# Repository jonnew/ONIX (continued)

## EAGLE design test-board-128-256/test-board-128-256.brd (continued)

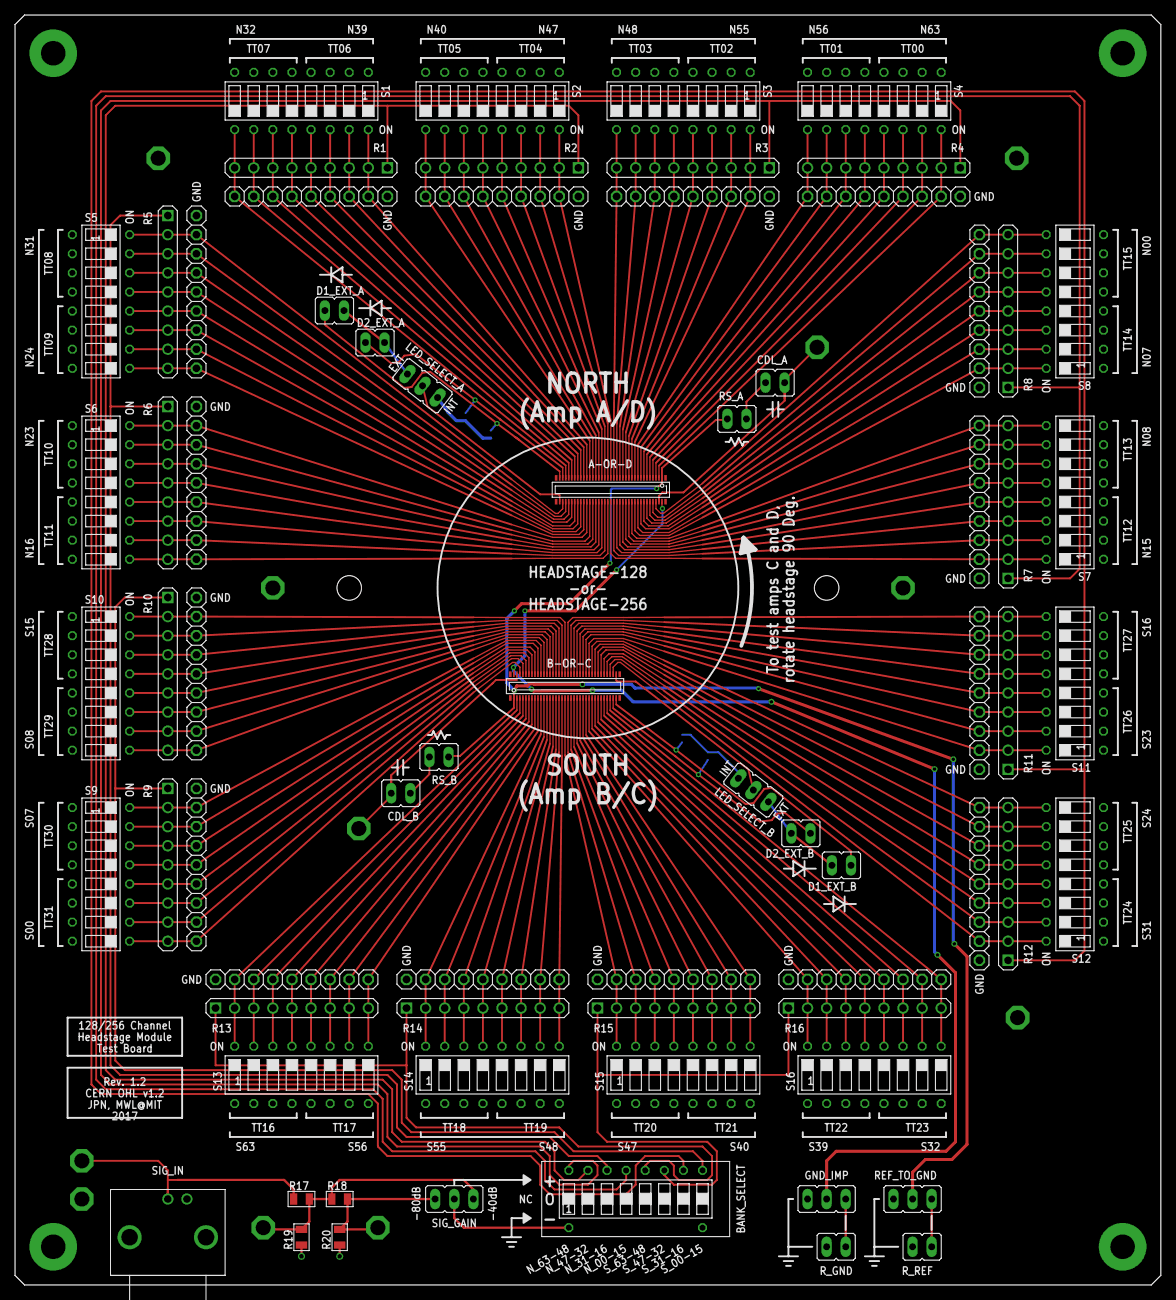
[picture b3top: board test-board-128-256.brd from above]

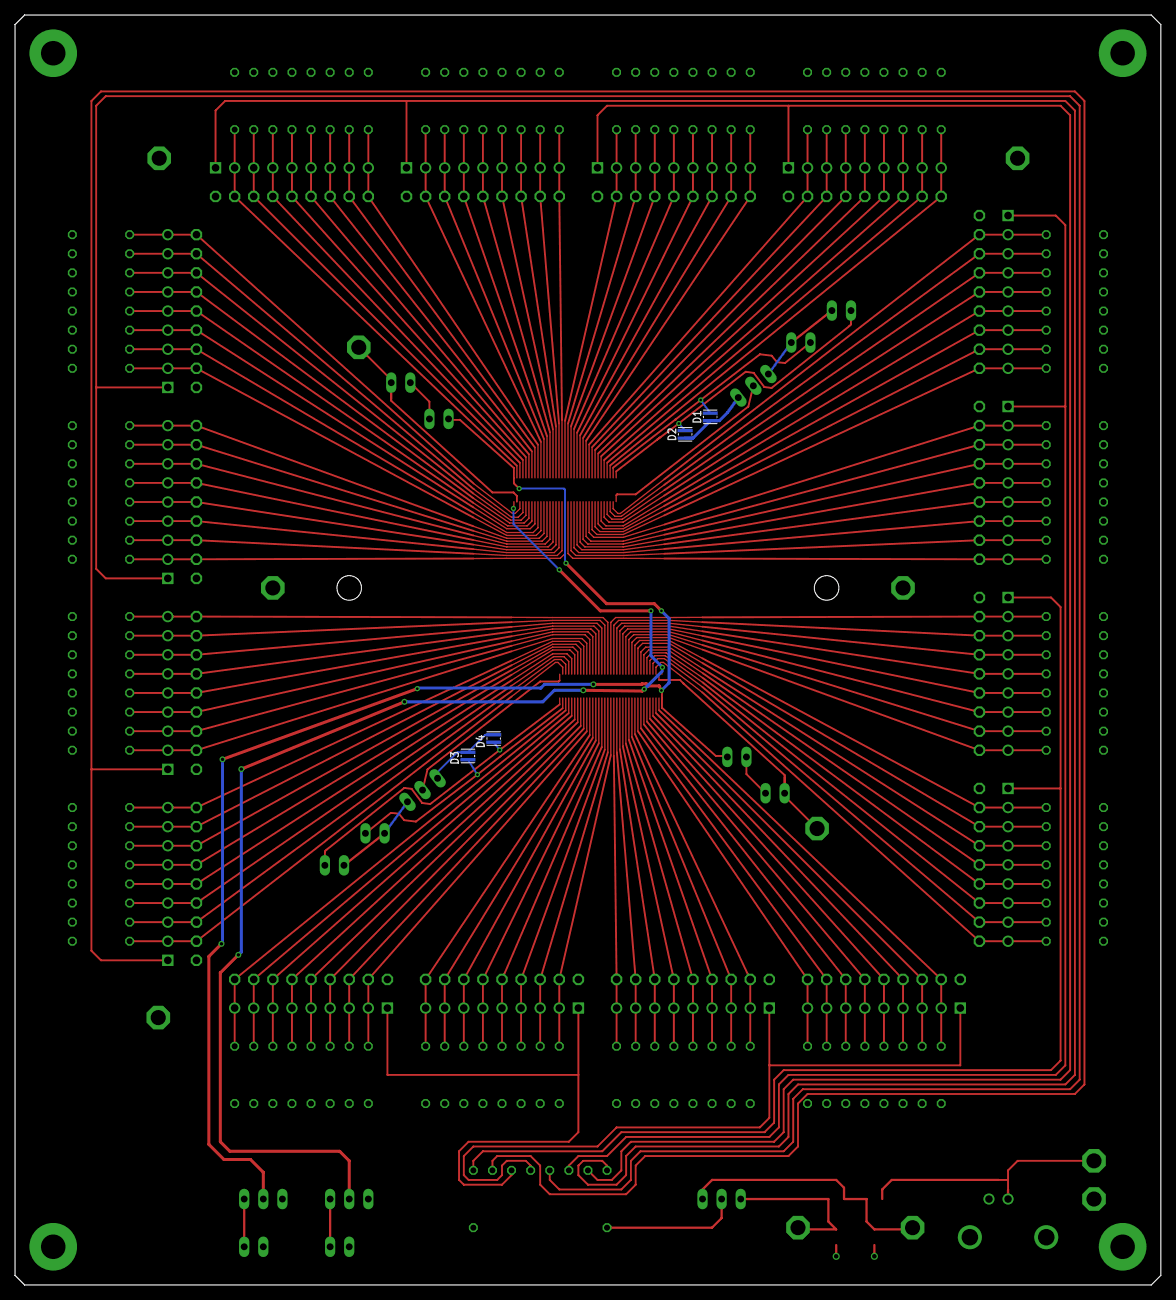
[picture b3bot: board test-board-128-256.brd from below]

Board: 2 copper layers, 152.4 x 168.9 mm, 90 parts (4 on the bottom side), 159 nets.

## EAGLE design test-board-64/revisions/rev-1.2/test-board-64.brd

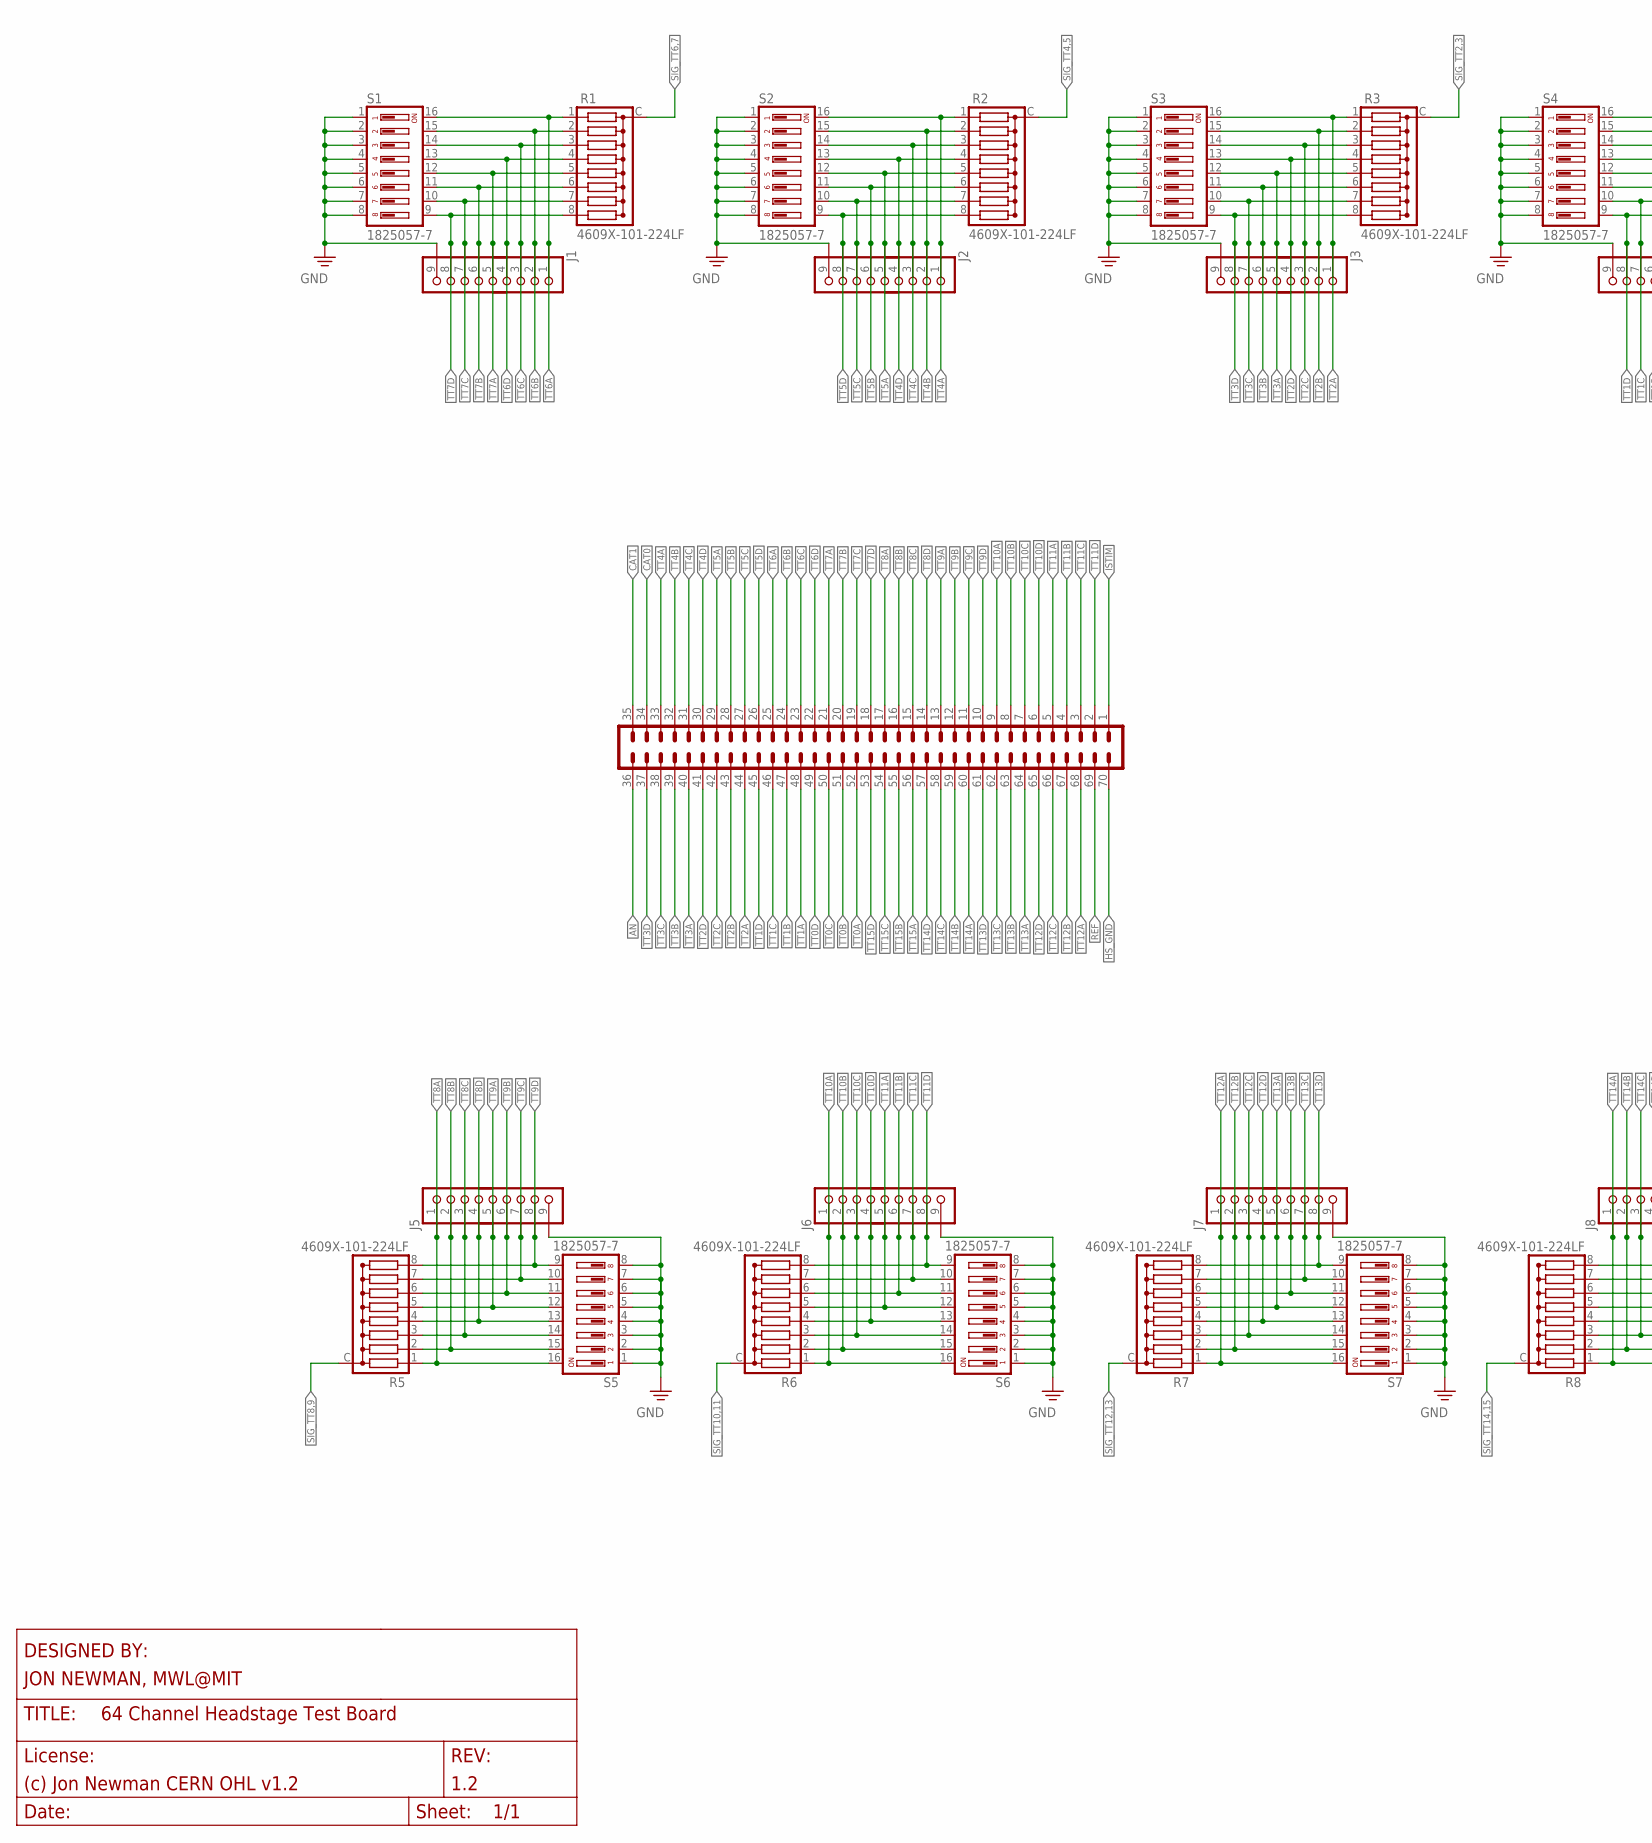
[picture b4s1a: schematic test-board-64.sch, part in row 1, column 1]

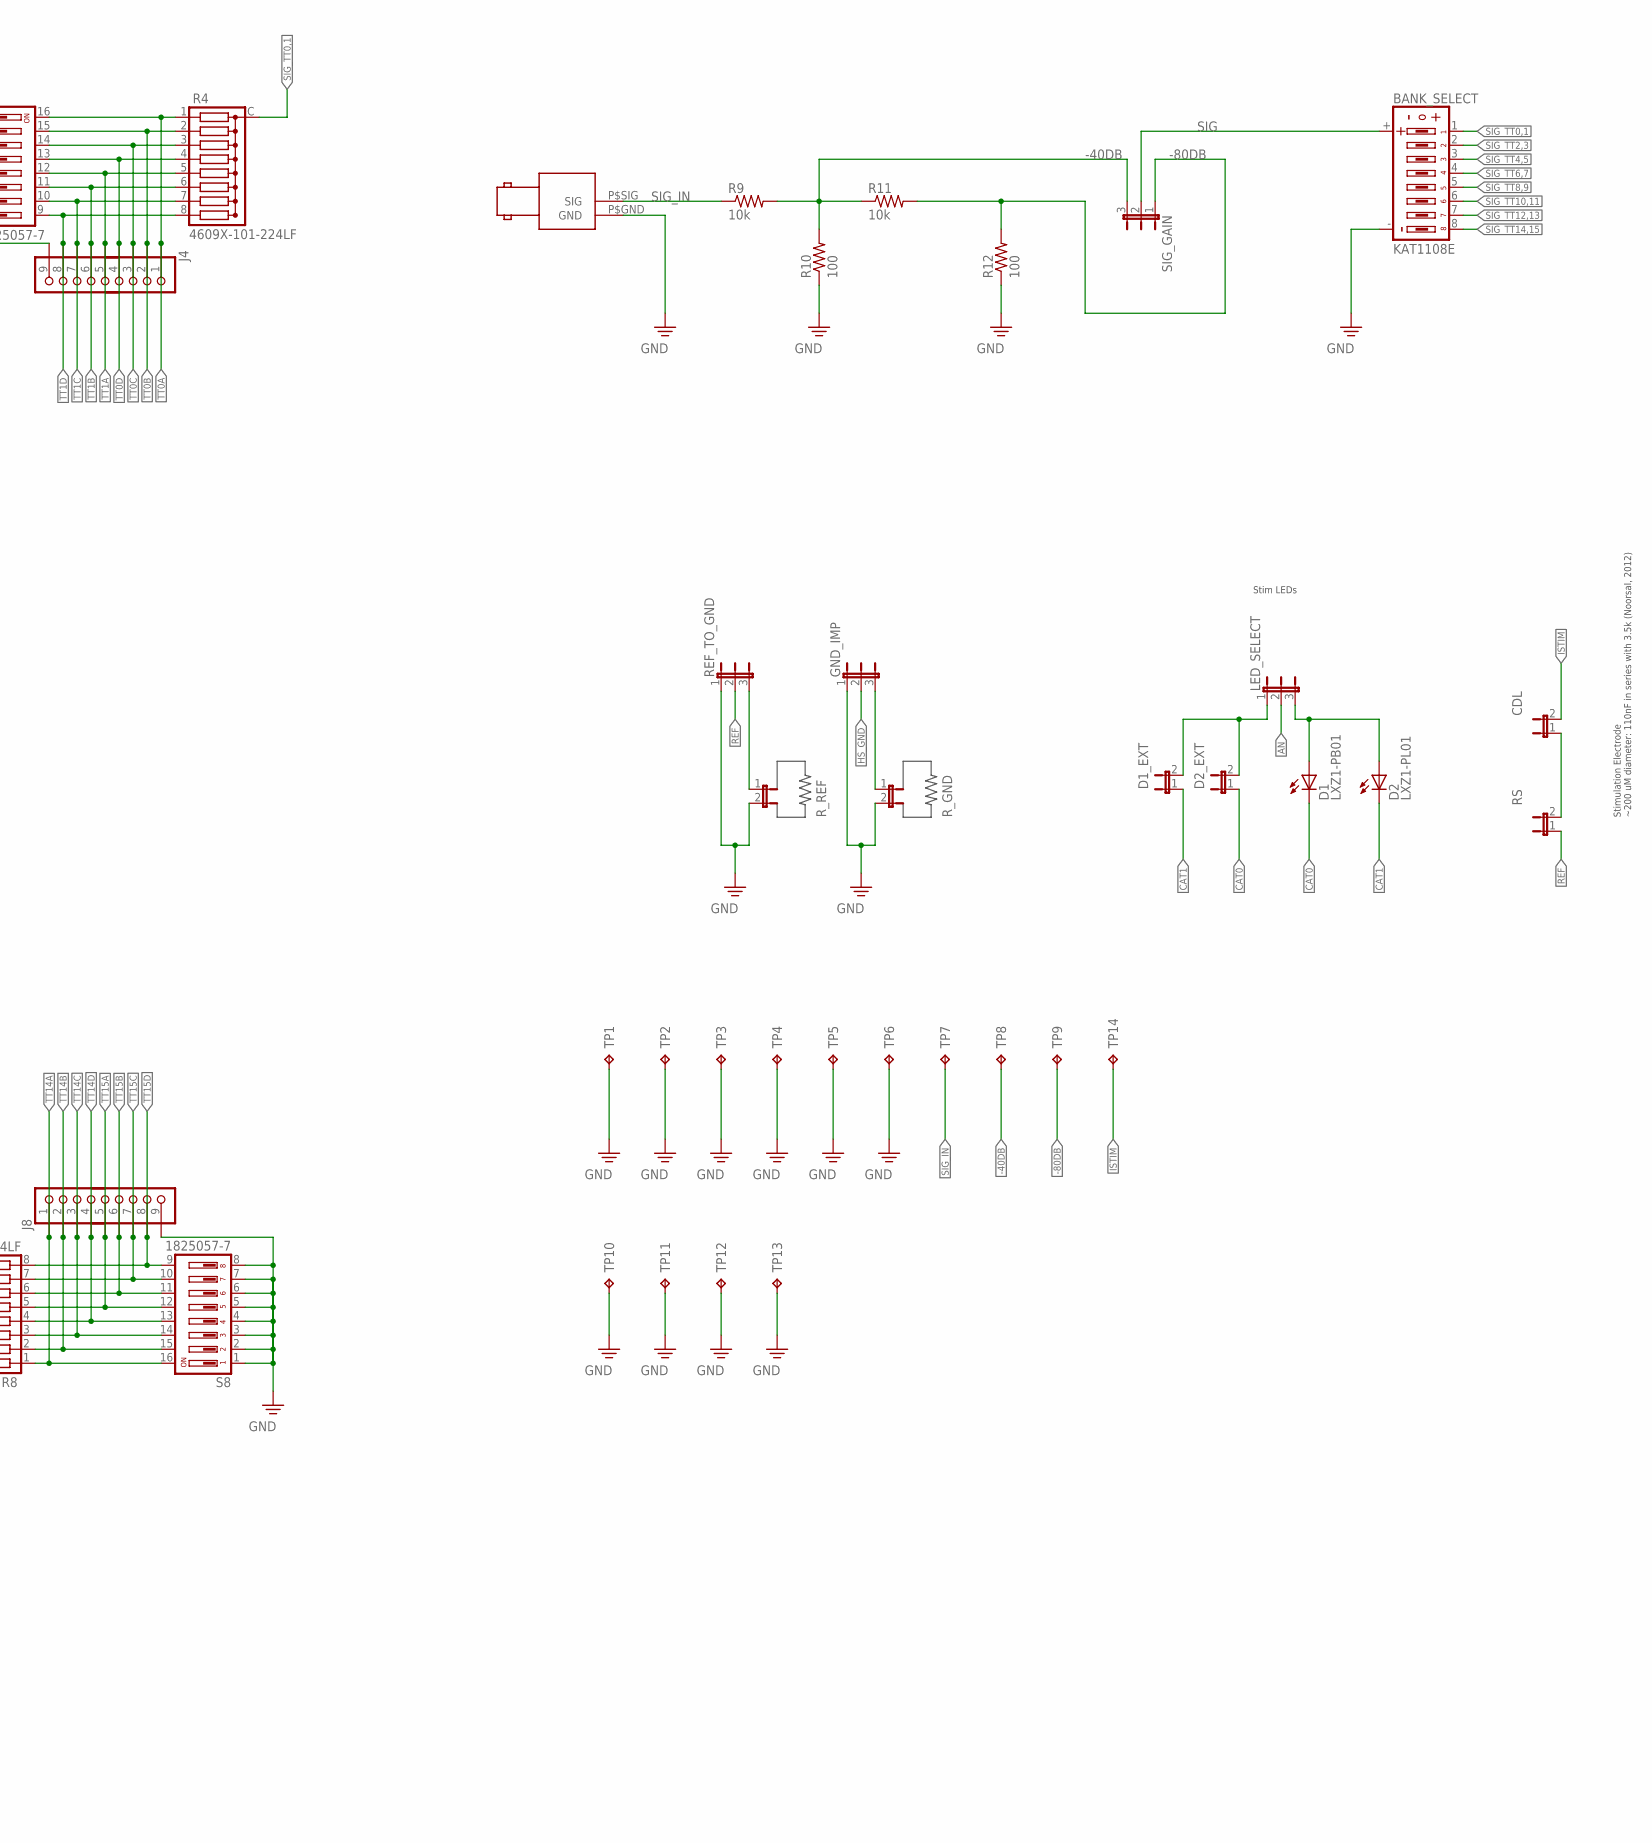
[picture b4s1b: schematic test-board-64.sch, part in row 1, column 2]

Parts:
BANK_SELECT: KAT1108E; 206-124_DIP8-SPDT
CDL: SOC2-0.1"; JP2
D1: LXZ1-PB01; LXZ1
D1_EXT, D2_EXT: SOC2-0.1"; JP2
D2: LXZ1-PL01; LXZ1
GND_IMP: JP3-0.1"; JP3
HEADSTAGE: DF40C-70DP-0.4V(51); DDF40-70REC-LRG
J1, J2, J3, J4, J5, J6, J7, J8: PINHD-1X9; 1X09
LED_SELECT: JP3-0.1"; JP3
R1, R2, R3, R4, R5, R6, R7, R8: 4609X-101-224LF; RNX8-0.1
R9, R11: 10k; 0805
R10, R12: 100; 0805
REF_TO_GND: JP3-0.1"; JP3
RS: SOC2-0.1"; JP2
R_GND: SOC2-0.1"; JP2
R_REF: SOC2-0.1"; JP2
S1, S2, S3, S4, S5, S6, S7, S8: 1825057-7; ADE_DIP8-SPST
SIG_GAIN: JP3-0.1"; JP3
SIG_IN: 1-1634622-0; BNC_RIGHT_ANGLE
TP1, TP2, TP3, TP4, TP5, TP6: GND; P1-20
TP7: SIG_IN; P1-20
TP8: -40dB; P1-20
TP9: -80dB; P1-20
TP10, TP11, TP12, TP13: TP_4-40; 4-40_PLATED
TP14: V_ESTIM; P1-20

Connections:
-40DB: R9.2, R10.2, R11.1, SIG_GAIN.3, TP8.TP
-80DB: R11.2, R12.2, SIG_GAIN.1, TP9.TP
AN: HEADSTAGE.36, LED_SELECT.2
AN_INT: D1.A, D2.A, LED_SELECT.3
CAT0: D1.C, D2_EXT.1, HEADSTAGE.34
CAT1: D1_EXT.1, D2.C, HEADSTAGE.35
GND: BANK_SELECT.-, GND_IMP.1, J1.9, J2.9, J3.9, J4.9, J5.9, J6.9, J7.9, J8.9, R10.1, R12.1, REF_TO_GND.1, R_GND.2, R_REF.2, S1.1, S1.2, S1.3, S1.4, S1.5, S1.6, S1.7, S1.8, S2.1, S2.2, S2.3, S2.4, S2.5, S2.6, S2.7, S2.8, S3.1, S3.2, S3.3, S3.4, S3.5, S3.6, S3.7, S3.8, S4.1, S4.2, S4.3, S4.4, S4.5, S4.6, S4.7, S4.8, S5.1, S5.2, S5.3, S5.4, S5.5, S5.6, S5.7, S5.8, S6.1, S6.2, S6.3, S6.4, S6.5, S6.6, S6.7, S6.8, S7.1, S7.2, S7.3, S7.4, S7.5, S7.6, S7.7, S7.8, S8.1, S8.2, S8.3, S8.4, S8.5, S8.6, S8.7, S8.8, SIG_IN.P$GND (GND), TP1.TP, TP2.TP, TP3.TP, TP4.TP, TP5.TP, TP6.TP, TP10.P$1, TP11.P$1, TP12.P$1, TP13.P$1
HS_GND: GND_IMP.2, HEADSTAGE.70
ISTIM: CDL.2, HEADSTAGE.1, TP14.TP
unnamed: D1_EXT.2, D2_EXT.2, LED_SELECT.1
unnamed: GND_IMP.3, R_GND.1
unnamed: CDL.1, RS.2
unnamed: REF_TO_GND.3, R_REF.1
REF: HEADSTAGE.69, REF_TO_GND.2, RS.1
SIG: BANK_SELECT.+, SIG_GAIN.2
SIG_IN: R9.1, SIG_IN.P$SIG (SIG), TP7.TP
SIG_TT0,1: BANK_SELECT.1, R4.C
SIG_TT2,3: BANK_SELECT.2, R3.C
SIG_TT4,5: BANK_SELECT.3, R2.C
SIG_TT6,7: BANK_SELECT.4, R1.C
SIG_TT8,9: BANK_SELECT.5, R5.C
SIG_TT10,11: BANK_SELECT.6, R6.C
SIG_TT12,13: BANK_SELECT.7, R7.C
SIG_TT14,15: BANK_SELECT.8, R8.C
TT0A: HEADSTAGE.52, J4.1, R4.1, S4.16
TT0B: HEADSTAGE.51, J4.2, R4.2, S4.15
TT0C: HEADSTAGE.50, J4.3, R4.3, S4.14
TT0D: HEADSTAGE.49, J4.4, R4.4, S4.13
TT1A: HEADSTAGE.48, J4.5, R4.5, S4.12
TT1B: HEADSTAGE.47, J4.6, R4.6, S4.11
TT1C: HEADSTAGE.46, J4.7, R4.7, S4.10
TT1D: HEADSTAGE.45, J4.8, R4.8, S4.9
TT2A: HEADSTAGE.44, J3.1, R3.1, S3.16
TT2B: HEADSTAGE.43, J3.2, R3.2, S3.15
TT2C: HEADSTAGE.42, J3.3, R3.3, S3.14
TT2D: HEADSTAGE.41, J3.4, R3.4, S3.13
TT3A: HEADSTAGE.40, J3.5, R3.5, S3.12
TT3B: HEADSTAGE.39, J3.6, R3.6, S3.11
TT3C: HEADSTAGE.38, J3.7, R3.7, S3.10
TT3D: HEADSTAGE.37, J3.8, R3.8, S3.9
TT4A: HEADSTAGE.33, J2.1, R2.1, S2.16
TT4B: HEADSTAGE.32, J2.2, R2.2, S2.15
TT4C: HEADSTAGE.31, J2.3, R2.3, S2.14
TT4D: HEADSTAGE.30, J2.4, R2.4, S2.13
TT5A: HEADSTAGE.29, J2.5, R2.5, S2.12
TT5B: HEADSTAGE.28, J2.6, R2.6, S2.11
TT5C: HEADSTAGE.27, J2.7, R2.7, S2.10
TT5D: HEADSTAGE.26, J2.8, R2.8, S2.9
TT6A: HEADSTAGE.25, J1.1, R1.1, S1.16
TT6B: HEADSTAGE.24, J1.2, R1.2, S1.15
TT6C: HEADSTAGE.23, J1.3, R1.3, S1.14
TT6D: HEADSTAGE.22, J1.4, R1.4, S1.13
TT7A: HEADSTAGE.21, J1.5, R1.5, S1.12
TT7B: HEADSTAGE.20, J1.6, R1.6, S1.11
TT7C: HEADSTAGE.19, J1.7, R1.7, S1.10
TT7D: HEADSTAGE.18, J1.8, R1.8, S1.9
TT8A: HEADSTAGE.17, J5.1, R5.1, S5.16
TT8B: HEADSTAGE.16, J5.2, R5.2, S5.15
TT8C: HEADSTAGE.15, J5.3, R5.3, S5.14
TT8D: HEADSTAGE.14, J5.4, R5.4, S5.13
TT9A: HEADSTAGE.13, J5.5, R5.5, S5.12
TT9B: HEADSTAGE.12, J5.6, R5.6, S5.11
TT9C: HEADSTAGE.11, J5.7, R5.7, S5.10
TT9D: HEADSTAGE.10, J5.8, R5.8, S5.9
TT10A: HEADSTAGE.9, J6.1, R6.1, S6.16
TT10B: HEADSTAGE.8, J6.2, R6.2, S6.15
TT10C: HEADSTAGE.7, J6.3, R6.3, S6.14
TT10D: HEADSTAGE.6, J6.4, R6.4, S6.13
TT11A: HEADSTAGE.5, J6.5, R6.5, S6.12
TT11B: HEADSTAGE.4, J6.6, R6.6, S6.11
TT11C: HEADSTAGE.3, J6.7, R6.7, S6.10
TT11D: HEADSTAGE.2, J6.8, R6.8, S6.9
TT12A: HEADSTAGE.68, J7.1, R7.1, S7.16
TT12B: HEADSTAGE.67, J7.2, R7.2, S7.15
TT12C: HEADSTAGE.66, J7.3, R7.3, S7.14
TT12D: HEADSTAGE.65, J7.4, R7.4, S7.13
TT13A: HEADSTAGE.64, J7.5, R7.5, S7.12
TT13B: HEADSTAGE.63, J7.6, R7.6, S7.11
TT13C: HEADSTAGE.62, J7.7, R7.7, S7.10
TT13D: HEADSTAGE.61, J7.8, R7.8, S7.9
TT14A: HEADSTAGE.60, J8.1, R8.1, S8.16
TT14B: HEADSTAGE.59, J8.2, R8.2, S8.15
TT14C: HEADSTAGE.58, J8.3, R8.3, S8.14
TT14D: HEADSTAGE.57, J8.4, R8.4, S8.13
TT15A: HEADSTAGE.56, J8.5, R8.5, S8.12
TT15B: HEADSTAGE.55, J8.6, R8.6, S8.11
TT15C: HEADSTAGE.54, J8.7, R8.7, S8.10
TT15D: HEADSTAGE.53, J8.8, R8.8, S8.9

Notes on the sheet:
Stimulation Electrode ~200 uM diameter: 110nF in series with 3.5k (Noorsal, 2012)
Stim LEDs

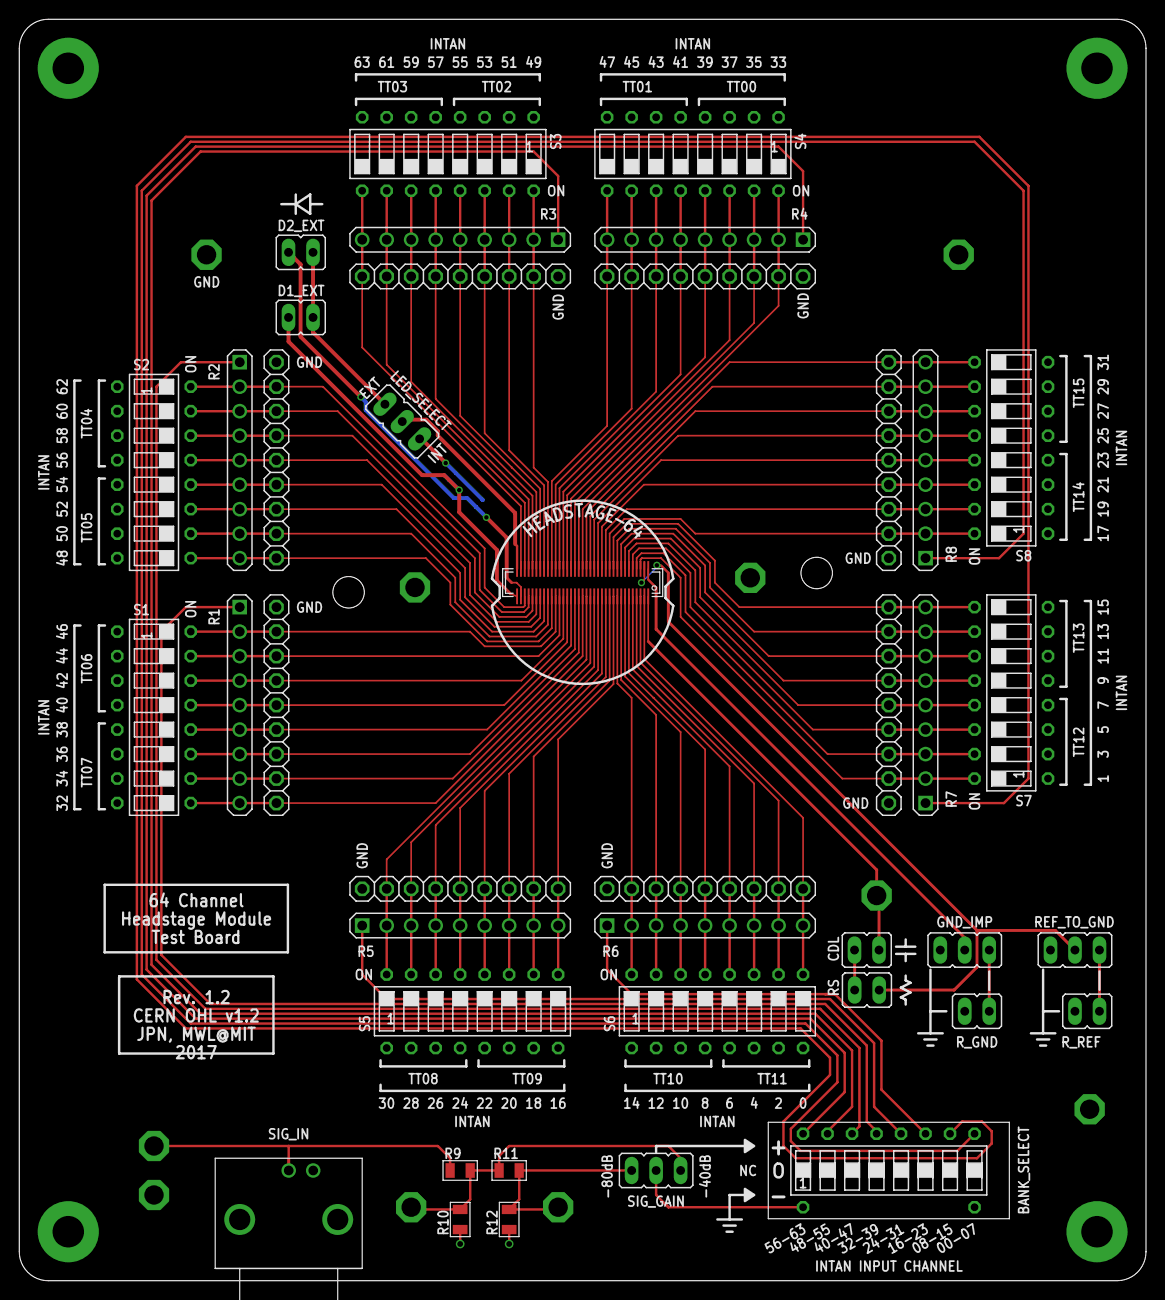
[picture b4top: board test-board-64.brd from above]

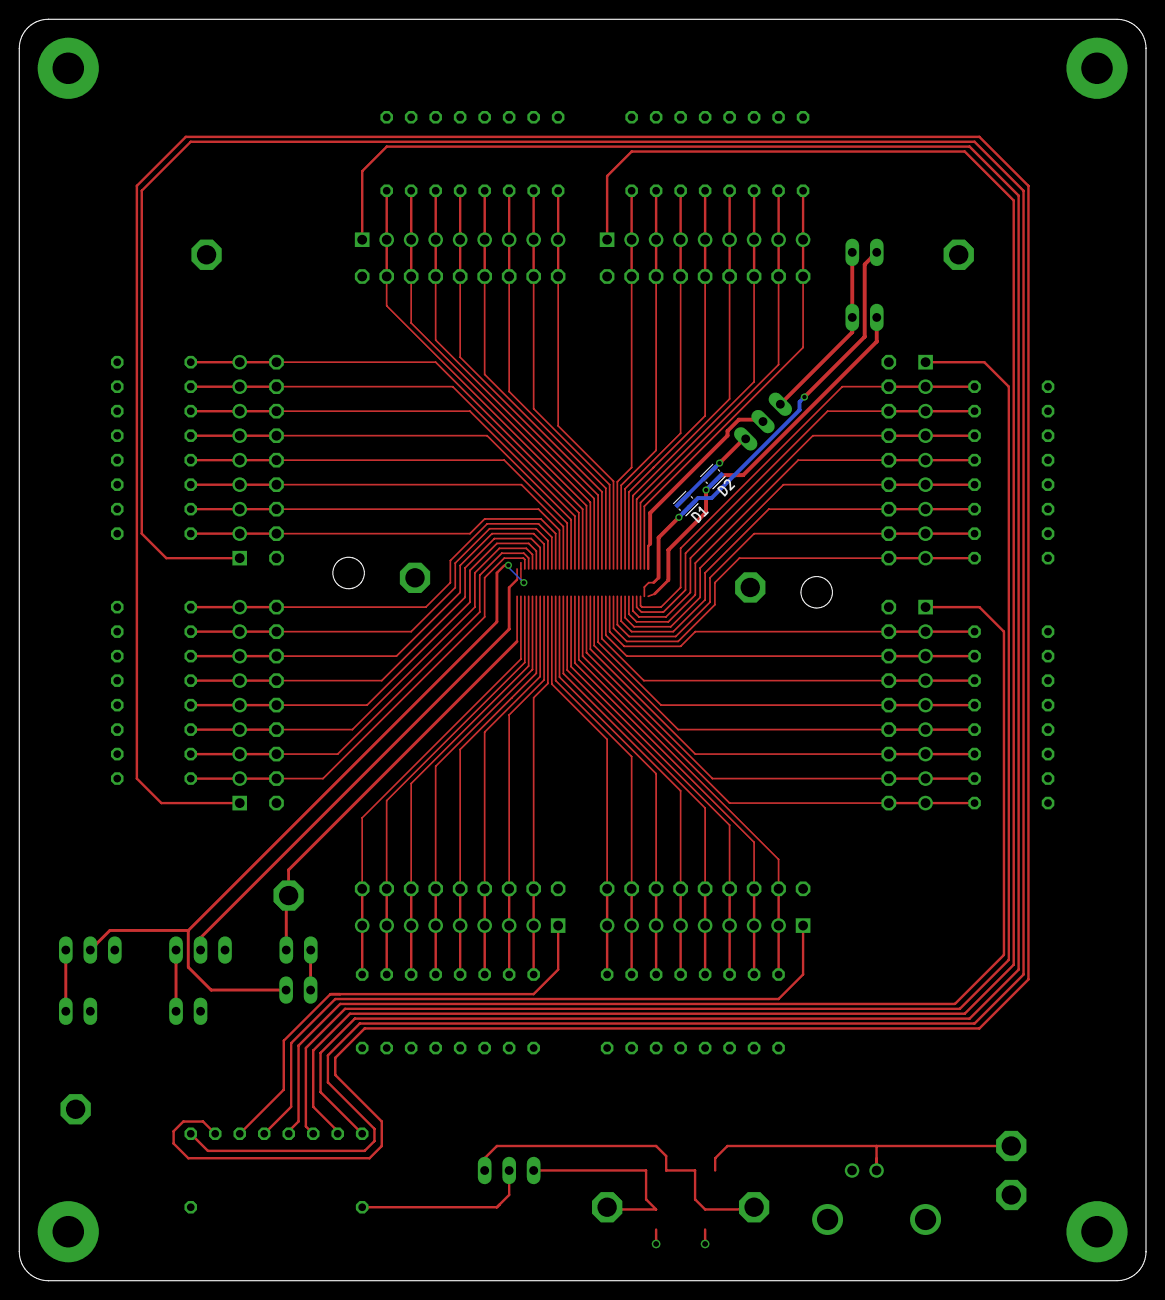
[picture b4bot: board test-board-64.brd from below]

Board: 2 copper layers, 116.8 x 130.8 mm, 57 parts (2 on the bottom side), 88 nets.
